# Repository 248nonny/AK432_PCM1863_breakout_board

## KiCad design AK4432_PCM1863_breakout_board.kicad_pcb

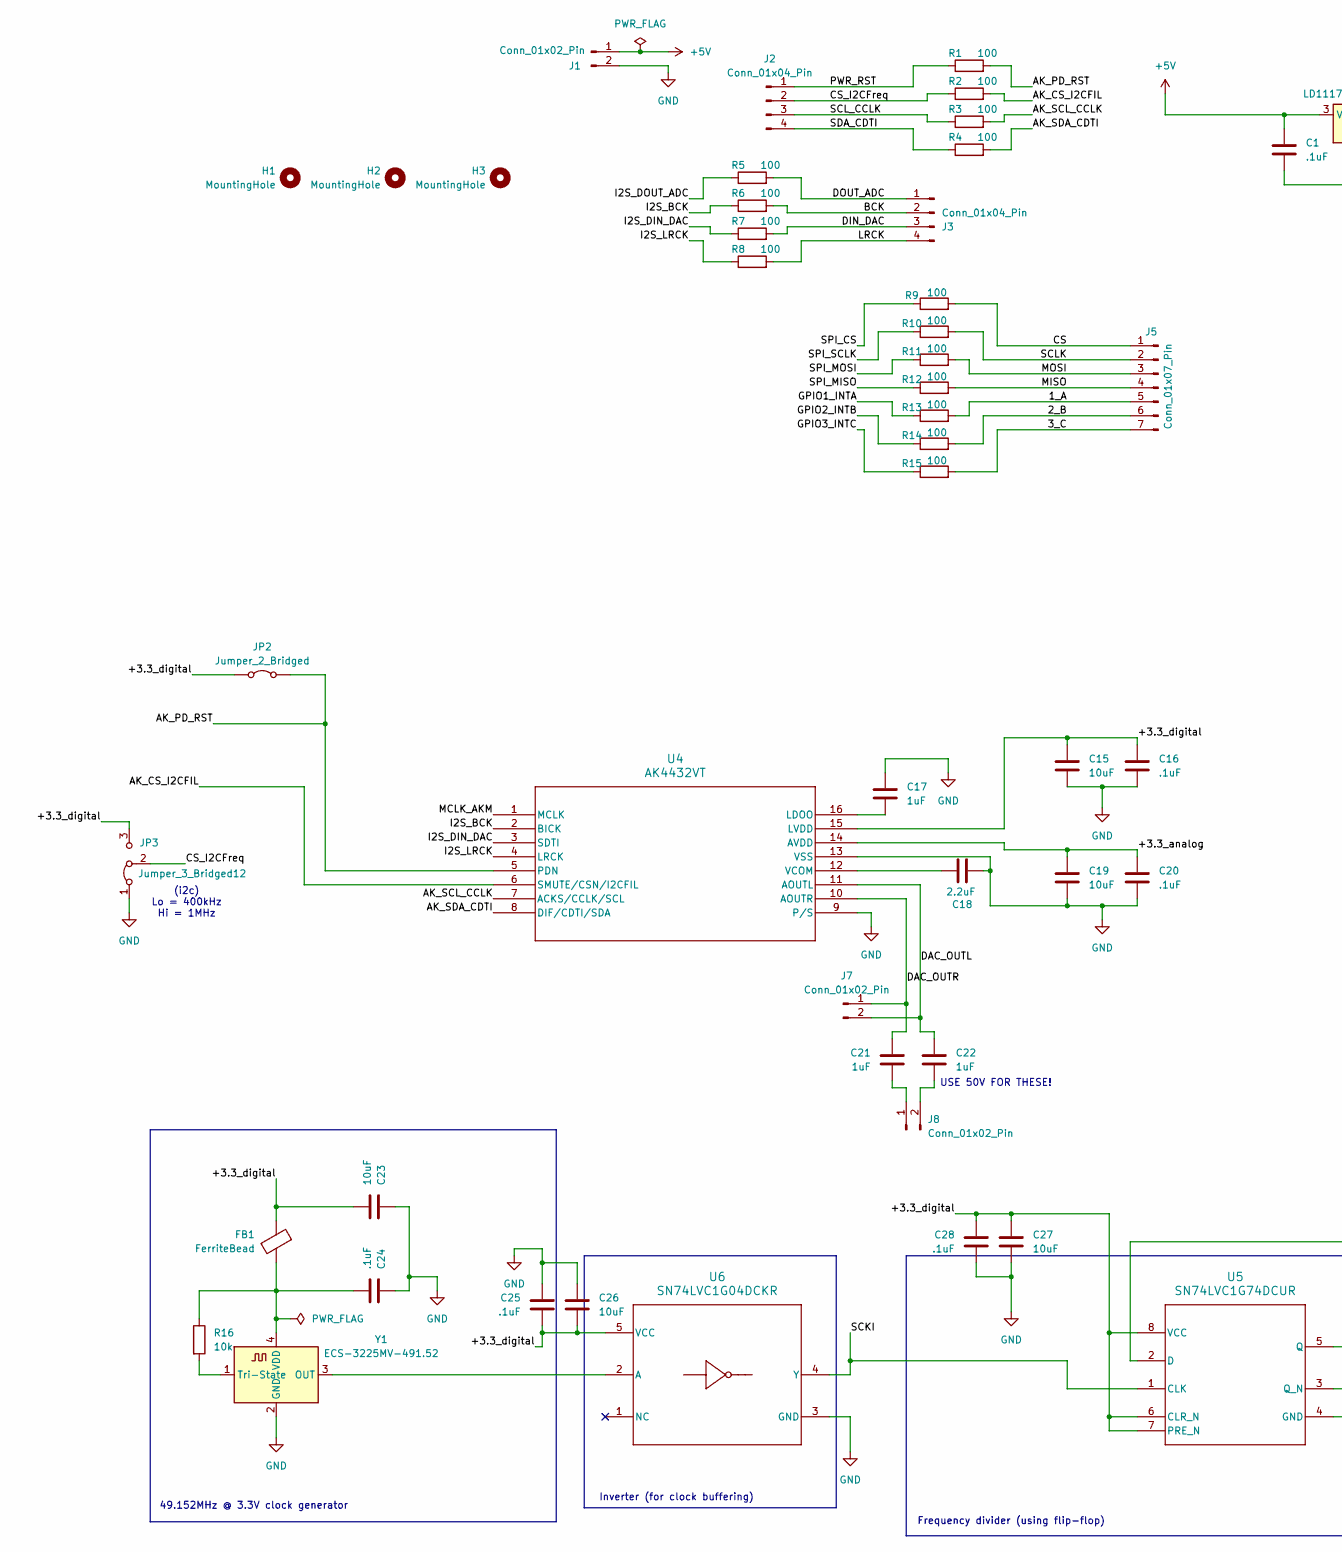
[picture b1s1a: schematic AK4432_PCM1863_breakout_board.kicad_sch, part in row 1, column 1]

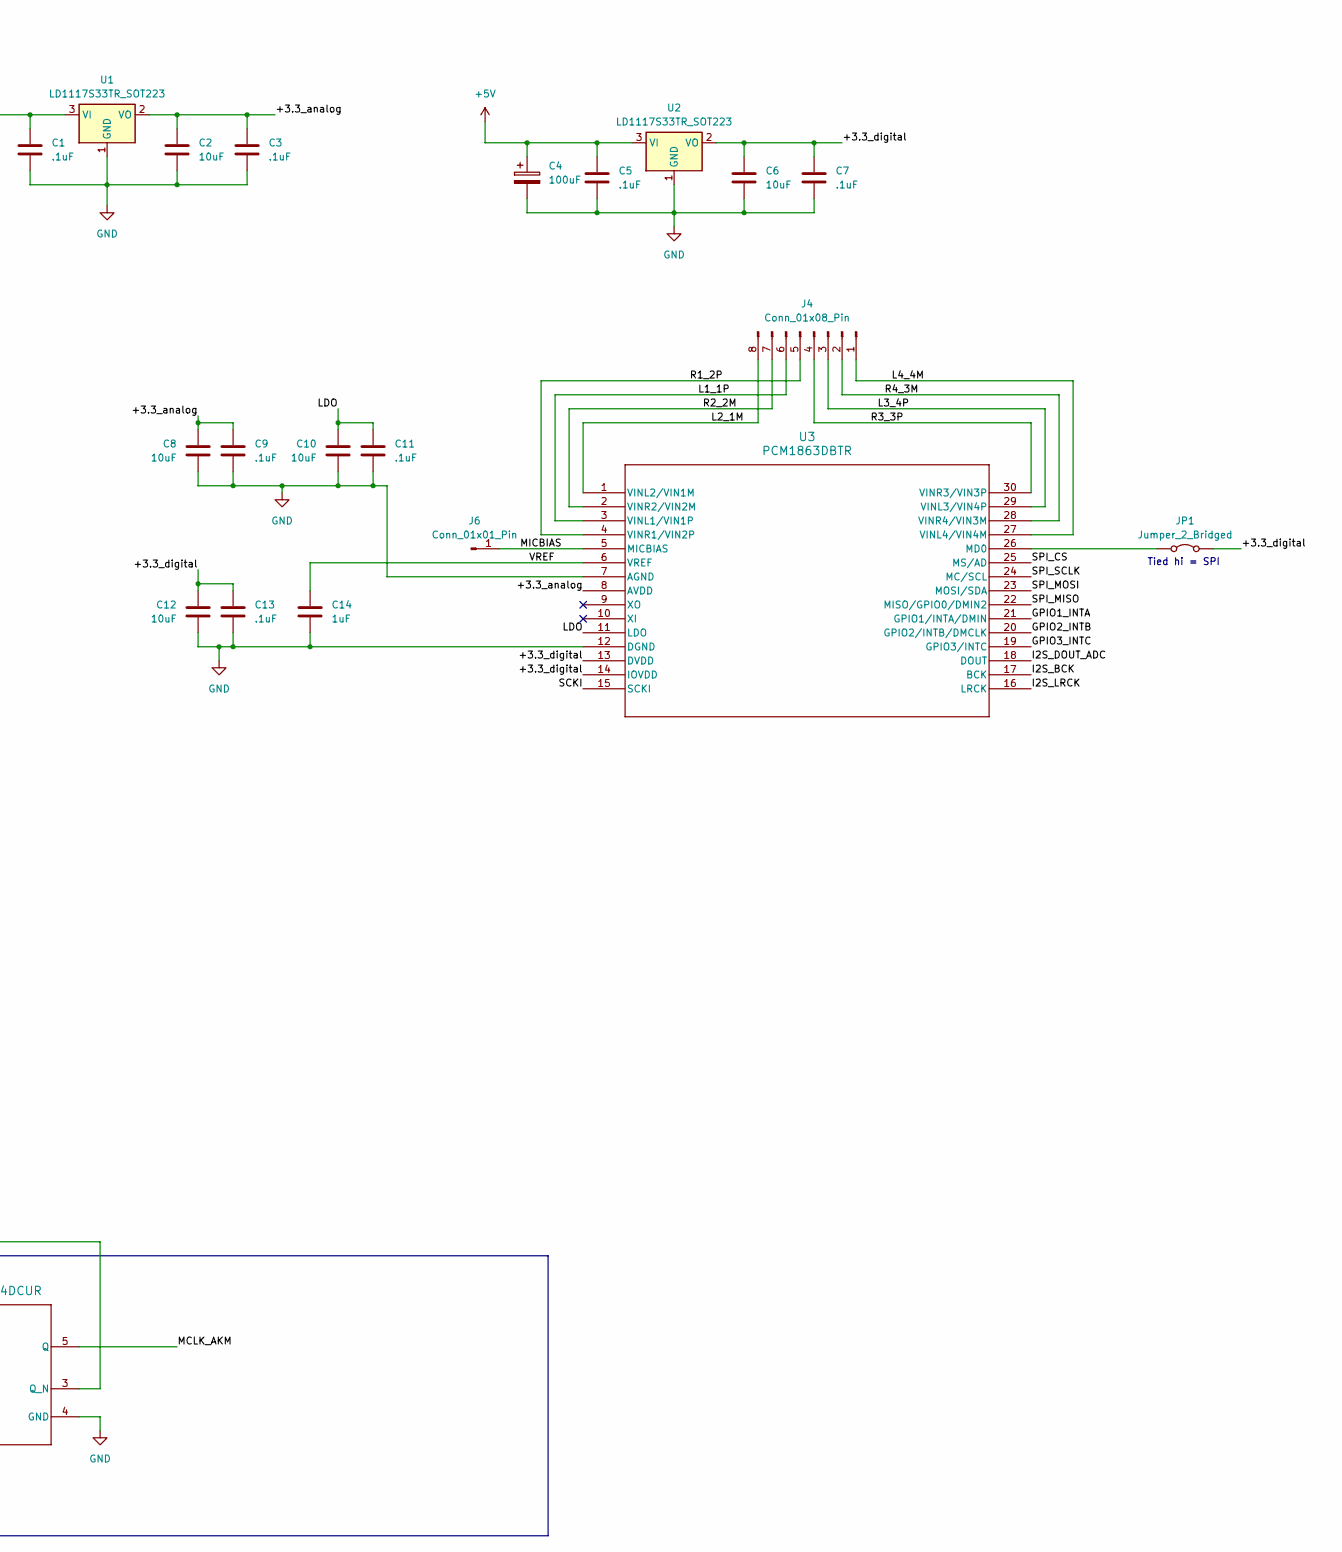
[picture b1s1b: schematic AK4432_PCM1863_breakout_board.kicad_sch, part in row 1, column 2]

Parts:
C1, C3, C5, C7, C9, C11, C13, C16, C20, C24, C25, C28: .1uF; C_0805_2012Metric_Pad1.18x1.45mm_HandSolder
C2, C6, C8, C10, C12, C15, C19, C23, C26, C27: 10uF; C_0805_2012Metric_Pad1.18x1.45mm_HandSolder
C4: 100uF; CP_Radial_D6.3mm_P2.50mm
C14: 1uF; C_0201_0603Metric_Pad0.64x0.40mm_HandSolder
C17, C21, C22: 1uF; C_0603_1608Metric_Pad1.08x0.95mm_HandSolder
C18: 2.2uF; C_0603_1608Metric_Pad1.08x0.95mm_HandSolder
FB1: FerriteBead; R_0402_1005Metric_Pad0.72x0.64mm_HandSolder
H1, H2, H3: MountingHole; MountingHole_3.2mm_M3
J1, J7, J8: Conn_01x02_Pin; PinHeader_1x02_P2.54mm_Vertical
J2, J3: Conn_01x04_Pin; PinHeader_1x04_P2.54mm_Vertical
J4: Conn_01x08_Pin; PinHeader_1x08_P2.54mm_Vertical
J5: Conn_01x07_Pin; PinHeader_1x07_P2.54mm_Vertical
J6: Conn_01x01_Pin; PinHeader_1x01_P2.54mm_Vertical
JP1, JP2: Jumper_2_Bridged; PinHeader_1x02_P2.54mm_Vertical
JP3: Jumper_3_Bridged12; PinHeader_1x03_P2.54mm_Vertical
R1, R2, R3, R4, R5, R6, R7, R8, R9, R10, R11, R12, R13, R14, R15: 100; R_0603_1608Metric_Pad0.98x0.95mm_HandSolder
R16: 10k; R_0402_1005Metric_Pad0.72x0.64mm_HandSolder
U1, U2: LD1117S33TR_SOT223; SOT-223-3_TabPin2
U3: PCM1863DBTR; DBT30_TEX-M
U4: AK4432VT; TSSOP16_AKM-M
U5: SN74LVC1G74DCUR; DCU0008A_N
U6: SN74LVC1G04DCKR; DCK0005A_M
Y1: ECS-3225MV-491.52; Oscillator_SMD_EuroQuartz_XO32-4Pin_3.2x2.5mm_HandSoldering

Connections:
+5V: C1.1, C4.1, C5.1, J1.1, U1.3 (VI), U2.3 (VI)
/1_A: J5.5, R13.2
/2_B: J5.6, R14.2
/3_C: J5.7, R15.2
/+3.3_analog: C2.1, C3.1, C8.1, C9.1, C19.1, C20.1, U1.2 (VO), U3.8 (AVDD), U4.14 (AVDD)
/+3.3_digital: C6.1, C7.1, C12.1, C13.1, C15.1, C16.1, C23.2, C25.2, C26.2, C27.1, C28.1, FB1.1, JP1.2 (B), JP2.2 (B), JP3.3 (B), U2.2 (VO), U3.13 (DVDD), U3.14 (IOVDD), U4.15 (LVDD), U5.6 (CLR_N), U5.7 (PRE_N), U5.8 (VCC), U6.5 (VCC)
/AK_CS_I2CFIL: R2.2, U4.6 (SMUTE/CSN/I2CFIL)
/AK_PD_RST: JP2.1 (A), R1.2, U4.5 (PDN)
/AK_SCL_CCLK: R3.2, U4.7 (ACKS/CCLK/SCL)
/AK_SDA_CDTI: R4.2, U4.8 (DIF/CDTI/SDA)
/BCK: J3.2, R6.2
/CS: J5.1, R9.2
/CS_I2CFreq: J2.2, JP3.2 (C), R2.1
/DAC_OUTL: C22.2, J7.2, U4.11 (AOUTL)
/DAC_OUTR: C21.2, J7.1, U4.10 (AOUTR)
/DIN_DAC: J3.3, R7.2
/DOUT_ADC: J3.1, R5.2
/GPIO1_INTA: R13.1, U3.21 (GPIO1/INTA/DMIN)
/GPIO2_INTB: R14.1, U3.20 (GPIO2/INTB/DMCLK)
/GPIO3_INTC: R15.1, U3.19 (GPIO3/INTC)
/I2S_BCK: R6.1, U3.17 (BCK), U4.2 (BICK)
/I2S_DIN_DAC: R7.1, U4.3 (SDTI)
/I2S_DOUT_ADC: R5.1, U3.18 (DOUT)
/I2S_LRCK: R8.1, U3.16 (LRCK), U4.4 (LRCK)
/L1_1P: J4.6, U3.3 (VINL1/VIN1P)
/L2_1M: J4.8, U3.1 (VINL2/VIN1M)
/L3_4P: J4.3, U3.29 (VINL3/VIN4P)
/L4_4M: J4.1, U3.27 (VINL4/VIN4M)
/LDO: C10.1, C11.1, U3.11 (LDO)
/LRCK: J3.4, R8.2
/MCLK_AKM: U4.1 (MCLK), U5.5 (Q)
/MICBIAS: J6.1, U3.5 (MICBIAS)
/MISO: J5.4, R12.2
/MOSI: J5.3, R11.2
/PWR_RST: J2.1, R1.1
/R1_2P: J4.5, U3.4 (VINR1/VIN2P)
/R2_2M: J4.7, U3.2 (VINR2/VIN2M)
/R3_3P: J4.4, U3.30 (VINR3/VIN3P)
/R4_3M: J4.2, U3.28 (VINR4/VIN3M)
/SCKI: U3.15 (SCKI), U5.1 (CLK), U6.4 (Y)
/SCLK: J5.2, R10.2
/SCL_CCLK: J2.3, R3.1
/SDA_CDTI: J2.4, R4.1
/SPI_CS: R9.1, U3.25 (MS/AD)
/SPI_MISO: R12.1, U3.22 (MISO/GPIO0/DMIN2)
/SPI_MOSI: R11.1, U3.23 (MOSI/SDA)
/SPI_SCLK: R10.1, U3.24 (MC/SCL)
/VREF: C14.1, U3.6 (VREF)
GND: C1.2, C2.2, C3.2, C4.2, C5.2, C6.2, C7.2, C8.2, C9.2, C10.2, C11.2, C12.2, C13.2, C14.2, C15.2, C16.2, C17.2, C18.1, C19.2, C20.2, C23.1, C24.1, C25.1, C26.1, C27.2, C28.2, J1.2, JP3.1 (A), U1.1 (GND), U2.1 (GND), U3.7 (AGND), U3.12 (DGND), U4.9 (P/S), U4.13 (VSS), U5.4 (GND), U6.3 (GND), Y1.2 (GND)
unnamed: C21.1, J8.1
unnamed: C22.1, J8.2
unnamed: JP1.1 (A), U3.26 (MD0)
unnamed: C17.1, U4.16 (LDOO)
unnamed: C18.2, U4.12 (VCOM)
unnamed: U5.2 (D), U5.3 (Q_N)
unnamed: U6.2 (A), Y1.3 (OUT)
unnamed: R16.2, Y1.1 (Tri-State)
unnamed: C24.2, FB1.2, R16.1, Y1.4 (VDD)

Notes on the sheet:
(i2c) Lo = 400kHz Hi = 1MHz
Tied hi = SPI
49.152MHz @ 3.3V clock generator
USE 50V FOR THESE!
Frequency divider (using flip-flop)
Inverter (for clock buffering)

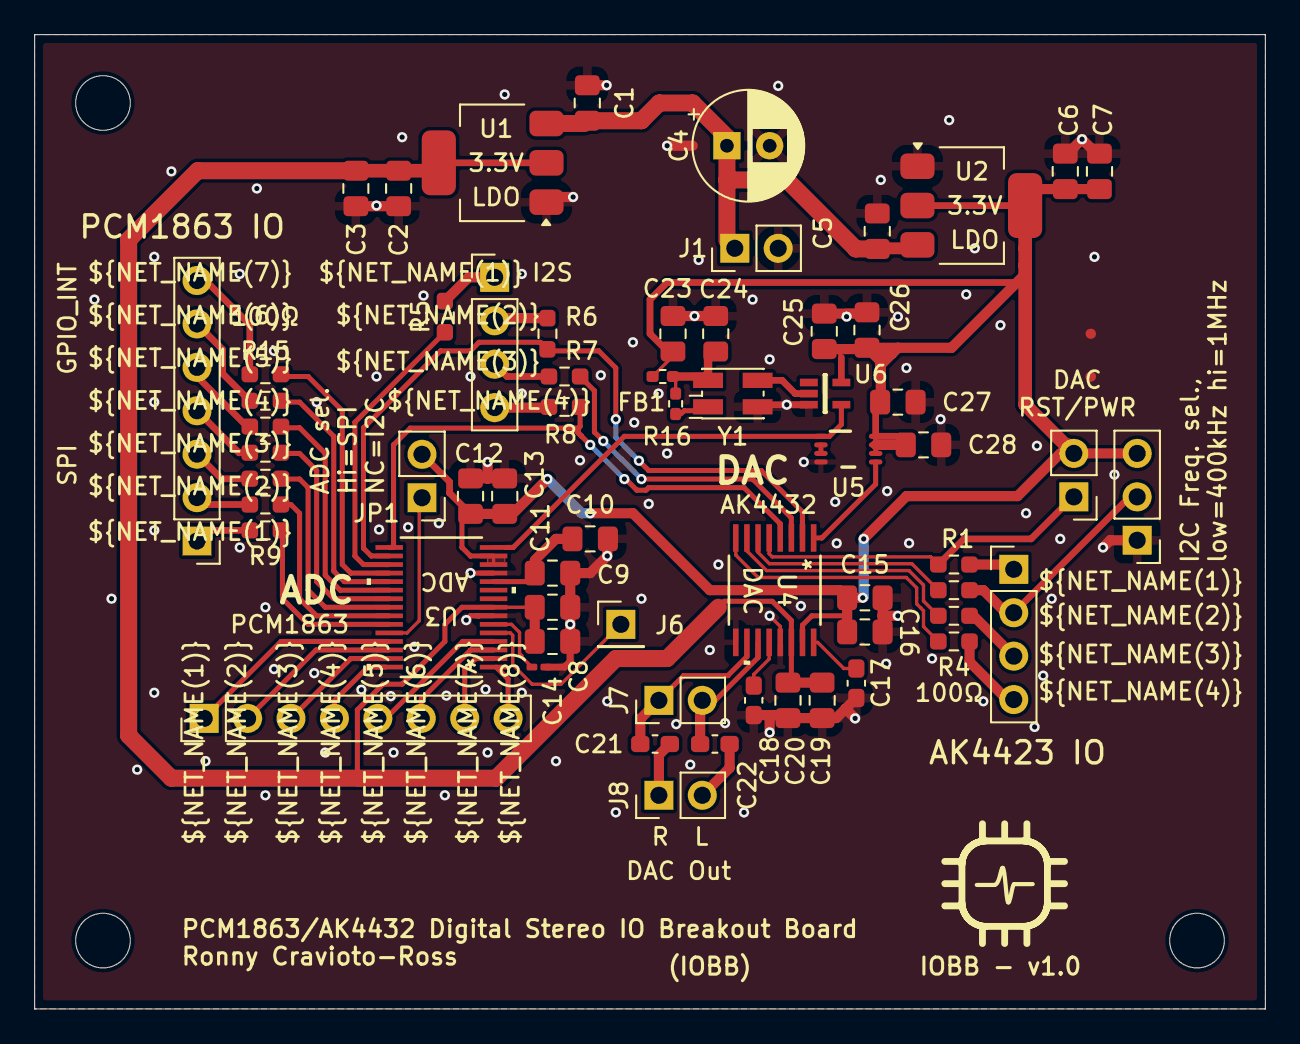
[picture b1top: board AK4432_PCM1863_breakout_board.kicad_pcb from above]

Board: 2 copper layers, 72.0 x 57.0 mm, 66 parts (0 on the bottom side), 58 nets.

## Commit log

2025-04-07 first commit!
2025-04-10 did some work :D
2025-04-12 did some work.
2025-04-12 finished preliminary schematic, started laying out.
2025-04-13 almost done laying out 2-layer prototype
2025-04-13 finished 2 layer layoutgit add -A
2025-04-14 Finished v1 layout! Also swaped flip-flop chip for a faster one.
2025-04-14 Made final v1 changes and ordered from JLC!
